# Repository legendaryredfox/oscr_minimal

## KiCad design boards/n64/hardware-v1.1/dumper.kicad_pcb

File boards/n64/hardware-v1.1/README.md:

# n64 v1.1

Versão **v1.1** da placa [`n64`](../README.md): shield 100% THT para Arduino Mega 2560 R3, só USB. Esta é a versão mais nova.

| | |
|---|---|
| Slots | N64 (50 pinos), 3,3 V |
| Circuitos | Si5351 só para a EEPROM. |
| Tamanho | 110,1 × 90,1 mm |
| Desligar o 5V por software | **sim** |
| Projeto KiCad | [`hardware-v1.1/`](.) (`dumper.kicad_pro`, `.kicad_sch`, `.kicad_pcb`) |
| Fábrica (JLCPCB) | `../fab/gerbers-v1.1/`, `../fab/dumper-v1.1-jlcpcb.zip` |
| Renders | `render-cima.png`, `render-baixo.png` |
| Estado | Nada montado nem testado com cartucho; revisar o layout no KiCad antes de encomendar |

## Troca de cartucho

**Com desligamento por software** (bloco de troca de cartucho, D126): o comando `POWER` liga e desliga o 5V dos slots, o rail é descarregado e o LED amarelo "SEGURO TROCAR" acende quando dá para tirar o cartucho. Circuito, peças e testes: [`docs/referencia/bloco-troca.md`](../../../docs/referencia/bloco-troca.md).

## Proteção de corrente e tensão (D138)

**F1: fusível de vidro 5×20 mm de 500 mA (ação rápida) em suporte de clipes, opcional.** O suporte é de furo passante (Littelfuse série 100 ou equivalente) e o fusível queimado se troca **sem solda**; fica em série com o 5 V que a placa recebe do Mega (nas versões com bloco de troca, antes do Q1). Um curto no cartucho queima o fusível e protege a placa, o Mega e a porta USB. A queda é de 0,1 a 0,2 V a 200 mA (o SA-1 do SNES continua abaixo de ~5,2 V). **Sem o fusível no suporte a placa fica sem 5 V** (um fio no lugar dele também serve). Ele limita corrente e não protege contra tensão errada.

## O que muda em relação à v1.0

| Peça | Referências | Antes | Agora |
|---|---|---|---|
| LED verde 3mm | D2 | 0 | 1 |
| LED amarelo 3mm | D3 | 0 | 1 |
| IRF9540N | Q1 | 0 | 1 |
| 2N7000 | Q2,Q3 | 0 | 2 |
| 100k | R3,R8 | 0 | 2 |
| 100R | R4 | 0 | 1 |
| 1k | R5,R9,R10 | 0 | 3 |
| 330R | R6,R7 | 0 | 2 |

## Lista de peças

| Referências | Valor | Footprint | Qtd |
|---|---|---|---|
| A1 | Mega2560_R3_Shield | `dumper:Mega2560_R3_Shield` | 1 |
| C1 | 470u/16V | `Capacitor_THT:CP_Radial_D8.0mm_P3.50mm` | 1 |
| C2,C3 | 1u | `Capacitor_THT:C_Disc_D5.0mm_W2.5mm_P5.00mm` | 2 |
| C4 | 100n | `Capacitor_THT:C_Disc_D5.0mm_W2.5mm_P5.00mm` | 1 |
| D1 | LED 3mm | `LED_THT:LED_D3.0mm` | 1 |
| D2 | LED verde 3mm | `LED_THT:LED_D3.0mm` | 1 |
| D3 | LED amarelo 3mm | `LED_THT:LED_D3.0mm` | 1 |
| F1 | Fusivel 5x20 500mA | `Fuse:Fuseholder_Littelfuse_100_series_5x20mm` | 1 |
| FLG1,FLG2 | PWR_FLAG | `` | 2 |
| N64_1 | N64_Slot | `dumper:N64_Slot` | 1 |
| Q1 | IRF9540N | `Package_TO_SOT_THT:TO-220-3_Vertical` | 1 |
| Q2,Q3 | 2N7000 | `Package_TO_SOT_THT:TO-92_Inline` | 2 |
| R1 | 220R | `Resistor_THT:R_Axial_DIN0207_L6.3mm_D2.5mm_P10.16mm_Horizontal` | 1 |
| R2 | 1k | `Resistor_THT:R_Axial_DIN0207_L6.3mm_D2.5mm_P10.16mm_Horizontal` | 1 |
| R3,R8 | 100k | `Resistor_THT:R_Axial_DIN0204_L3.6mm_D1.6mm_P2.54mm_Vertical` | 2 |
| R4 | 100R | `Resistor_THT:R_Axial_DIN0204_L3.6mm_D1.6mm_P2.54mm_Vertical` | 1 |
| R5,R9,R10 | 1k | `Resistor_THT:R_Axial_DIN0204_L3.6mm_D1.6mm_P2.54mm_Vertical` | 3 |
| R6,R7 | 330R | `Resistor_THT:R_Axial_DIN0204_L3.6mm_D1.6mm_P2.54mm_Vertical` | 2 |
| U1 | Si5351_Module | `Connector_PinSocket_2.54mm:PinSocket_1x07_P2.54mm_Vertical` | 1 |
| U2 | MCP1700-3302E/TO (3,3 V) | `Package_TO_SOT_THT:TO-92` | 1 |

Gerada do esquemático desta versão (`kicad-cli sch export bom`). Peças marcadas DNP ou opcionais: `docs/componentes-opcionais.md` da placa.

## Verificação e fábrica (da raiz do repositório)

```
python3 tools/check_netlist.py --board n64
kicad-cli sch erc boards/n64/hardware-v1.1/dumper.kicad_sch
kicad-cli pcb drc boards/n64/hardware-v1.1/dumper.kicad_pcb
tools/export_fab.sh n64 v1.1
tools/render_board.sh n64 v1.0 v1.1
```

Mais: [README da placa](../README.md), [`docs/`](../docs/).

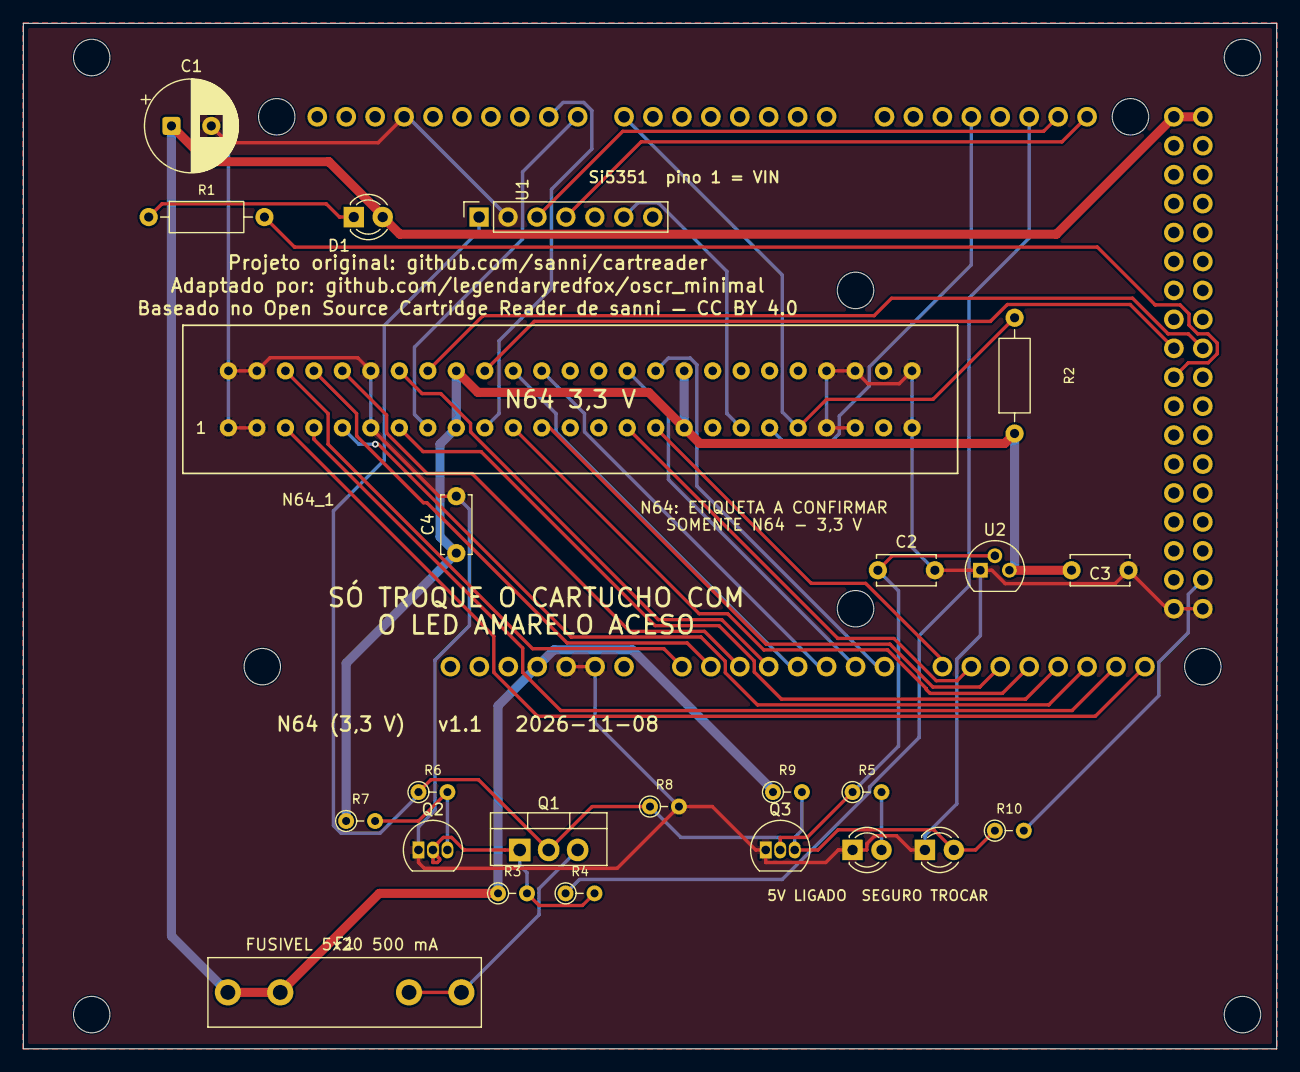
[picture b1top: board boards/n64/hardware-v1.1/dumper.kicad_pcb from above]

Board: 2 copper layers, 110.0 x 90.0 mm, 29 parts (0 on the bottom side), 38 nets.

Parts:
A1: Mega2560_R3_Shield
C1: 470u/16V; CP_Radial_D8.0mm_P3.50mm
C2, C3: 1u; C_Disc_D5.0mm_W2.5mm_P5.00mm
C4: 100n; C_Disc_D5.0mm_W2.5mm_P5.00mm
D1: LED 3mm; LED_D3.0mm
D2: LED verde 3mm; LED_D3.0mm
D3: LED amarelo 3mm; LED_D3.0mm
F1: Fusivel 5x20 500mA; Fuseholder_Littelfuse_100_series_5x20mm
MH1, MH2, MH3, MH4: MountingHole_3.2mm; MountingHole_3.2mm_M3
N64_1: N64_Slot
Q1: IRF9540N; TO-220-3_Vertical
Q2, Q3: 2N7000; TO-92_Inline
R1: 220R; R_Axial_DIN0207_L6.3mm_D2.5mm_P10.16mm_Horizontal
R2: 1k; R_Axial_DIN0207_L6.3mm_D2.5mm_P10.16mm_Horizontal
R3, R8: 100k; R_Axial_DIN0204_L3.6mm_D1.6mm_P2.54mm_Vertical
R4: 100R; R_Axial_DIN0204_L3.6mm_D1.6mm_P2.54mm_Vertical
R5, R9, R10: 1k; R_Axial_DIN0204_L3.6mm_D1.6mm_P2.54mm_Vertical
R6, R7: 330R; R_Axial_DIN0204_L3.6mm_D1.6mm_P2.54mm_Vertical
U1: Si5351_Module; PinSocket_1x07_P2.54mm_Vertical
U2: MCP1700-3302E/TO (3,3 V); TO-92

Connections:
+3V3: C3.1, C4.1, N64_1.9, N64_1.17, N64_1.34, N64_1.42, R2.1, R7.1, U2.3
+5V: A1.5V1, A1.5V3, A1.5V4, C1.1, D1.2, F1.1, R3.1, R9.1
+5V_CART: C2.1, Q1.2, Q3.2, R5.1, R6.1, R8.1, U1.1, U2.2
+5V_F: F1.2, Q1.3
/A0: A1.A0, N64_1.28
/A1: A1.A1, N64_1.29
/A2: A1.A2, N64_1.30
/A3: A1.A3, N64_1.32
/A4: A1.A4, N64_1.36
/A5: A1.A5, N64_1.37
/A6: A1.A6, N64_1.40
/A7: A1.A7, N64_1.41
/A8: A1.A8, N64_1.16
/A9: A1.A9, N64_1.15
/A10: A1.A10, N64_1.12
/A11: A1.A11, N64_1.11
/A12: A1.A12, N64_1.7
/A13: A1.A13, N64_1.5
/A14: A1.A14, N64_1.4
/A15: A1.A15, N64_1.3
/CLK1: N64_1.19, U1.6
/D7: A1.D7, N64_1.21, R2.2
/D8: A1.D8, N64_1.8
/D9: A1.D9, N64_1.10
/D17: A1.D17, N64_1.20
/D36: A1.D36, N64_1.35
/D37: A1.D37, N64_1.33
/PWR_EN: A1.D19, R4.1
/PWR_G: Q1.1, Q2.2, R3.2, R4.2
/SENSE: D3.2, Q3.3, R9.2, R10.1
/SENSE_MCU: A1.D53, R10.2
GND: A1.GND1, A1.GND2, A1.GND3, A1.GND5, A1.GND6, C1.2, C2.2, C3.2, C4.2, D2.1, D3.1, N64_1.1, N64_1.2, N64_1.6, N64_1.22, N64_1.23, N64_1.25, N64_1.26, N64_1.27, N64_1.31, N64_1.47, N64_1.48, N64_1.50, Q2.1, Q3.1, R8.2, U1.2, U2.1
unnamed: A1.D38, R1.2
unnamed: D1.1, R1.1
unnamed: D2.2, R5.2
unnamed: Q2.3, R6.2, R7.2
unnamed: A1.D21, U1.4
unnamed: A1.D20, U1.3

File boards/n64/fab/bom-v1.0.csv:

"Ref","Valor","Footprint","Qtd"
"A1","Mega2560_R3_Shield","dumper:Mega2560_R3_Shield","1"
"C1","470u/16V","Capacitor_THT:CP_Radial_D8.0mm_P3.50mm","1"
"C2,C3","1u","Capacitor_THT:C_Disc_D5.0mm_W2.5mm_P5.00mm","2"
"C4","100n","Capacitor_THT:C_Disc_D5.0mm_W2.5mm_P5.00mm","1"
"D1","LED 3mm","LED_THT:LED_D3.0mm","1"
"F1","Fusivel 5x20 500mA","Fuse:Fuseholder_Littelfuse_100_series_5x20mm","1"
"FLG1,FLG2","PWR_FLAG","","2"
"N64_1","N64_Slot","dumper:N64_Slot","1"
"R1","220R","Resistor_THT:R_Axial_DIN0207_L6.3mm_D2.5mm_P10.16mm_Horizontal","1"
"R2","1k","Resistor_THT:R_Axial_DIN0207_L6.3mm_D2.5mm_P10.16mm_Horizontal","1"
"U1","Si5351_Module","Connector_PinSocket_2.54mm:PinSocket_1x07_P2.54mm_Vertical","1"
"U2","MCP1700-3302E/TO (3,3 V)","Package_TO_SOT_THT:TO-92","1"

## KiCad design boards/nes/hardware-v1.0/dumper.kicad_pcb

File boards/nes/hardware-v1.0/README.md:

# nes v1.0

Versão **v1.0** da placa [`nes`](../README.md): shield 100% THT para Arduino Mega 2560 R3, só USB. Versão anterior, mantida ao lado da mais nova.

| | |
|---|---|
| Slots | NES (72p, 2,5 mm), 5 V |
| Circuitos | Si5351 (clock do slot), sem PIC. |
| Tamanho | 110,1 × 61,1 mm |
| Projeto KiCad | [`hardware-v1.0/`](.) (`dumper.kicad_pro`, `.kicad_sch`, `.kicad_pcb`) |
| Fábrica (JLCPCB) | `../fab/gerbers-v1.0/`, `../fab/dumper-v1.0-jlcpcb.zip` |
| Renders | `render-cima.png`, `render-baixo.png` |
| Mecânica | Sem os 6 furos M3 do Mega (só os 4 furos de canto); F1 entre o slot e o header do Mega, sem a faixa extra de baixo (D141) |
| Estado | Nada montado nem testado com cartucho; revisar o layout no KiCad antes de encomendar |

## Troca de cartucho

O 5V dos slots vai direto do Mega e **não é cortado por software** (o desligamento por software foi retirado, D139). Para trocar o cartucho, **desligue a placa tirando o cabo USB** do Mega; nunca com a USB ligada.

## Proteção de corrente e tensão (D138)

**F1: fusível de vidro 5×20 mm de 500 mA (ação rápida) em suporte de clipes, opcional.** O suporte é de furo passante (Littelfuse série 100 ou equivalente) e o fusível queimado se troca **sem solda**; fica em série com o 5 V que a placa recebe do Mega Um curto no cartucho queima o fusível e protege a placa, o Mega e a porta USB. A queda é de 0,1 a 0,2 V a 200 mA (o SA-1 do SNES continua abaixo de ~5,2 V). **Sem o fusível no suporte a placa fica sem 5 V** (um fio no lugar dele também serve). Ele limita corrente e não protege contra tensão errada.

## Lista de peças

| Referências | Valor | Footprint | Qtd |
|---|---|---|---|
| A1 | Mega2560_R3_Shield | `dumper:Mega2560_R3_Shield` | 1 |
| C1 | 470u/16V | `Capacitor_THT:CP_Radial_D8.0mm_P3.50mm` | 1 |
| C2 | 100n | `Capacitor_THT:C_Disc_D5.0mm_W2.5mm_P5.00mm` | 1 |
| D1 | LED 3mm | `LED_THT:LED_D3.0mm` | 1 |
| F1 | Fusivel 5x20 500mA | `Fuse:Fuseholder_Littelfuse_100_series_5x20mm` | 1 |
| FLG1,FLG2 | PWR_FLAG | `` | 2 |
| NES1 | NES_Slot | `dumper:NES_Slot` | 1 |
| R1 | 220R | `Resistor_THT:R_Axial_DIN0207_L6.3mm_D2.5mm_P10.16mm_Horizontal` | 1 |
| U1 | Si5351_Module | `Connector_PinSocket_2.54mm:PinSocket_1x07_P2.54mm_Vertical` | 1 |

Gerada do esquemático desta versão (`kicad-cli sch export bom`). Peças marcadas DNP ou opcionais: `docs/bom.md` da placa.

## Verificação e fábrica (da raiz do repositório)

```
python3 tools/check_netlist.py --board nes boards/nes/hardware-v1.0/dumper.kicad_sch
kicad-cli sch erc boards/nes/hardware-v1.0/dumper.kicad_sch
kicad-cli pcb drc boards/nes/hardware-v1.0/dumper.kicad_pcb
tools/export_fab.sh nes v1.0
tools/render_board.sh nes v1.0 v1.1
```

Mais: [README da placa](../README.md), [`docs/`](../docs/).

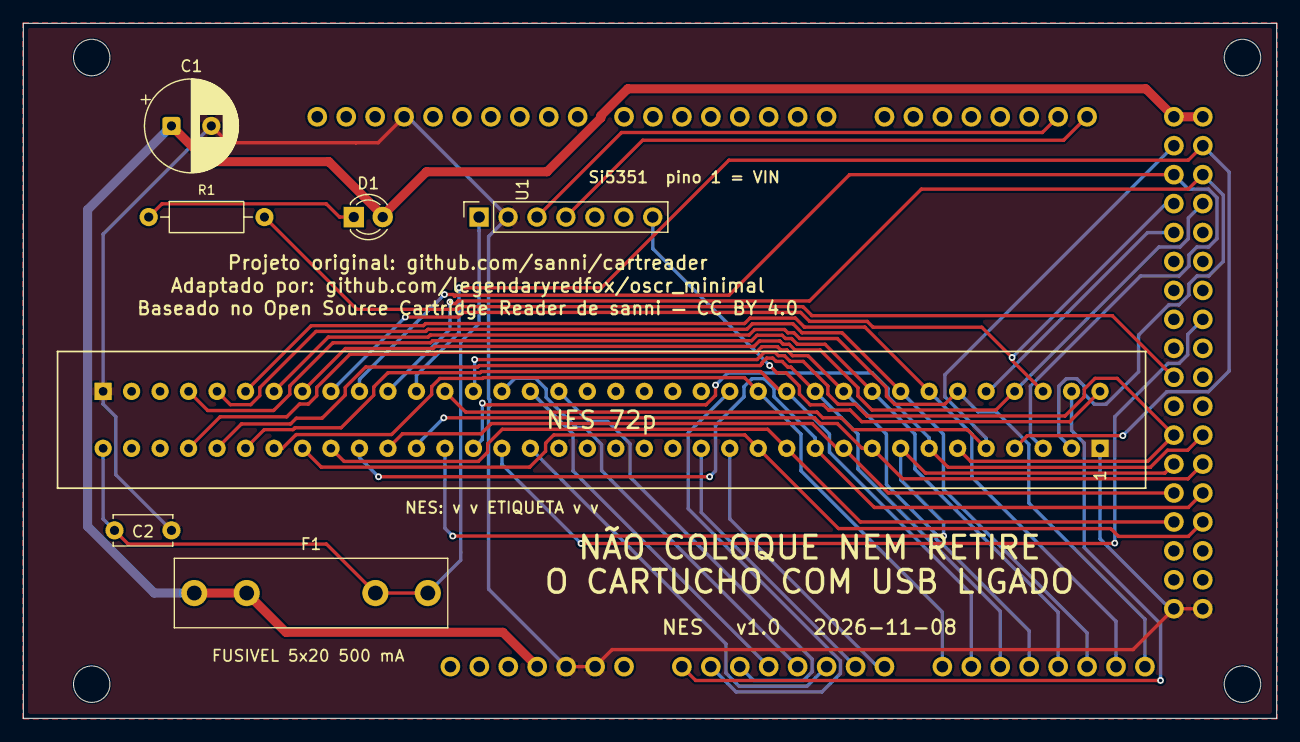
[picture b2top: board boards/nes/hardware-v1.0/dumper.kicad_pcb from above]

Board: 2 copper layers, 110.0 x 61.0 mm, 12 parts (0 on the bottom side), 40 nets.

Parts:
A1: Mega2560_R3_Shield
C1: 470u/16V; CP_Radial_D8.0mm_P3.50mm
C2: 100n; C_Disc_D5.0mm_W2.5mm_P5.00mm
D1: LED 3mm; LED_D3.0mm
F1: Fusivel 5x20 500mA; Fuseholder_Littelfuse_100_series_5x20mm
MH1, MH2, MH3, MH4: MountingHole_3.2mm; MountingHole_3.2mm_M3
NES1: NES_Slot
R1: 220R; R_Axial_DIN0207_L6.3mm_D2.5mm_P10.16mm_Horizontal
U1: Si5351_Module; PinSocket_1x07_P2.54mm_Vertical

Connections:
+5V: A1.5V1, A1.5V3, A1.5V4, C1.1, D1.2, F1.1
+5V_CART: C2.1, F1.2, NES1.36, U1.1
/A0: A1.A0, NES1.38
/A1: A1.A1, NES1.50
/A2: A1.A2, NES1.56
/A3: A1.A3, NES1.57
/A4: A1.A4, NES1.58
/A5: A1.A5, NES1.21
/A6: A1.A6, NES1.15
/A7: A1.A7, NES1.14
/A8: A1.A8, NES1.30, NES1.49
/A9: A1.A9, NES1.31, NES1.48
/A10: A1.A10, NES1.32, NES1.47
/A11: A1.A11, NES1.33, NES1.46
/A12: A1.A12, NES1.45, NES1.69
/A13: A1.A13, NES1.44, NES1.68
/A14: A1.A14, NES1.43, NES1.67
/A15: A1.A15, NES1.42, NES1.66
/CLK0: NES1.37, U1.7
/D22: A1.D22, NES1.5, NES1.60
/D23: A1.D23, NES1.4, NES1.61
/D24: A1.D24, NES1.3, NES1.63
/D25: A1.D25, NES1.2, NES1.62
/D26: A1.D26, NES1.39, NES1.64
/D27: A1.D27, NES1.40, NES1.65
/D28: A1.D28, NES1.41
/D35: A1.D35, NES1.22
/D42: A1.D42, NES1.6, NES1.59
/D43: A1.D43, NES1.7, NES1.23
/D44: A1.D44, NES1.8, NES1.24
/D45: A1.D45, NES1.9, NES1.25
/D46: A1.D46, NES1.10, NES1.26
/D47: A1.D47, NES1.11, NES1.27
/D48: A1.D48, NES1.12, NES1.28
/D49: A1.D49, NES1.13, NES1.29
GND: A1.GND1, A1.GND2, A1.GND3, A1.GND5, A1.GND6, C1.2, C2.2, NES1.1, NES1.72, U1.2
unnamed: A1.D38, R1.2
unnamed: D1.1, R1.1
unnamed: A1.D21, U1.4
unnamed: A1.D20, U1.3

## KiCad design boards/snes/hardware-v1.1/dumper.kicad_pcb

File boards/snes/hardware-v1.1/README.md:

# snes v1.1

Versão **v1.1** da placa [`snes`](../README.md): shield 100% THT para Arduino Mega 2560 R3, só USB. Esta é a versão mais nova.

| | |
|---|---|
| Slots | SNES (62p, 2,5 mm), 5 V |
| Circuitos | Si5351 em header fêmea e PIC12F629 (CIC) em soquete. |
| Tamanho | 107,1 × 90,1 mm |
| Desligar o 5V por software | **sim** |
| Projeto KiCad | [`hardware-v1.1/`](.) (`dumper.kicad_pro`, `.kicad_sch`, `.kicad_pcb`) |
| Fábrica (JLCPCB) | `../fab/gerbers-v1.1/`, `../fab/dumper-v1.1-jlcpcb.zip` |
| Renders | `render-cima.png`, `render-baixo.png` |
| Estado | Nada montado nem testado com cartucho; revisar o layout no KiCad antes de encomendar |

## Troca de cartucho

**Com desligamento por software** (bloco de troca de cartucho, D126): o comando `POWER` liga e desliga o 5V dos slots, o rail é descarregado e o LED amarelo "SEGURO TROCAR" acende quando dá para tirar o cartucho. Circuito, peças e testes: [`docs/referencia/bloco-troca.md`](../../../docs/referencia/bloco-troca.md).

## Proteção de corrente e tensão (D138)

**F1: fusível de vidro 5×20 mm de 500 mA (ação rápida) em suporte de clipes, opcional.** O suporte é de furo passante (Littelfuse série 100 ou equivalente) e o fusível queimado se troca **sem solda**; fica em série com o 5 V que a placa recebe do Mega (nas versões com bloco de troca, antes do Q1). Um curto no cartucho queima o fusível e protege a placa, o Mega e a porta USB. A queda é de 0,1 a 0,2 V a 200 mA (o SA-1 do SNES continua abaixo de ~5,2 V). **Sem o fusível no suporte a placa fica sem 5 V** (um fio no lugar dele também serve). Ele limita corrente e não protege contra tensão errada.

## O que muda em relação à v1.0

| Peça | Referências | Antes | Agora |
|---|---|---|---|
| LED verde 3mm | D2 | 0 | 1 |
| LED amarelo 3mm | D3 | 0 | 1 |
| IRF9540N | Q1 | 0 | 1 |
| 2N7000 | Q2,Q3 | 0 | 2 |
| 100k | R3,R7 | 0 | 2 |
| 100R | R4 | 0 | 1 |
| 1k | R5,R8,R9 | 0 | 3 |
| 330R | R6 | 0 | 1 |

## Lista de peças

| Referências | Valor | Footprint | Qtd |
|---|---|---|---|
| A1 | Mega2560_R3_Shield | `dumper:Mega2560_R3_Shield` | 1 |
| C1 | 470u/16V | `Capacitor_THT:CP_Radial_D8.0mm_P3.50mm` | 1 |
| C2,C3 | 100n | `Capacitor_THT:C_Disc_D5.0mm_W2.5mm_P5.00mm` | 2 |
| D1 | LED 3mm | `LED_THT:LED_D3.0mm` | 1 |
| D2 | LED verde 3mm | `LED_THT:LED_D3.0mm` | 1 |
| D3 | LED amarelo 3mm | `LED_THT:LED_D3.0mm` | 1 |
| F1 | Fusivel 5x20 500mA | `Fuse:Fuseholder_Littelfuse_100_series_5x20mm` | 1 |
| FLG1,FLG2 | PWR_FLAG | `` | 2 |
| Q1 | IRF9540N | `Package_TO_SOT_THT:TO-220-3_Vertical` | 1 |
| Q2,Q3 | 2N7000 | `Package_TO_SOT_THT:TO-92_Inline` | 2 |
| R1 | 220R | `Resistor_THT:R_Axial_DIN0207_L6.3mm_D2.5mm_P10.16mm_Horizontal` | 1 |
| R2 | 1k | `Resistor_THT:R_Axial_DIN0207_L6.3mm_D2.5mm_P10.16mm_Horizontal` | 1 |
| R3,R7 | 100k | `Resistor_THT:R_Axial_DIN0204_L3.6mm_D1.6mm_P2.54mm_Vertical` | 2 |
| R4 | 100R | `Resistor_THT:R_Axial_DIN0204_L3.6mm_D1.6mm_P2.54mm_Vertical` | 1 |
| R5,R8,R9 | 1k | `Resistor_THT:R_Axial_DIN0204_L3.6mm_D1.6mm_P2.54mm_Vertical` | 3 |
| R6 | 330R | `Resistor_THT:R_Axial_DIN0204_L3.6mm_D1.6mm_P2.54mm_Vertical` | 1 |
| SNES1 | SNES_Slot | `dumper:SNES_Slot` | 1 |
| U1 | Si5351_Module | `Connector_PinSocket_2.54mm:PinSocket_1x07_P2.54mm_Vertical` | 1 |
| U2 | PIC12F629 (em soquete; snescic-lock-resync) | `Package_DIP:DIP-8_W7.62mm` | 1 |

Gerada do esquemático desta versão (`kicad-cli sch export bom`). Peças marcadas DNP ou opcionais: `docs/componentes-opcionais.md` da placa.

## Verificação e fábrica (da raiz do repositório)

```
python3 tools/check_netlist.py --board snes
kicad-cli sch erc boards/snes/hardware-v1.1/dumper.kicad_sch
kicad-cli pcb drc boards/snes/hardware-v1.1/dumper.kicad_pcb
tools/export_fab.sh snes v1.1
tools/render_board.sh snes v1.0 v1.1
```

Mais: [README da placa](../README.md), [`docs/`](../docs/).

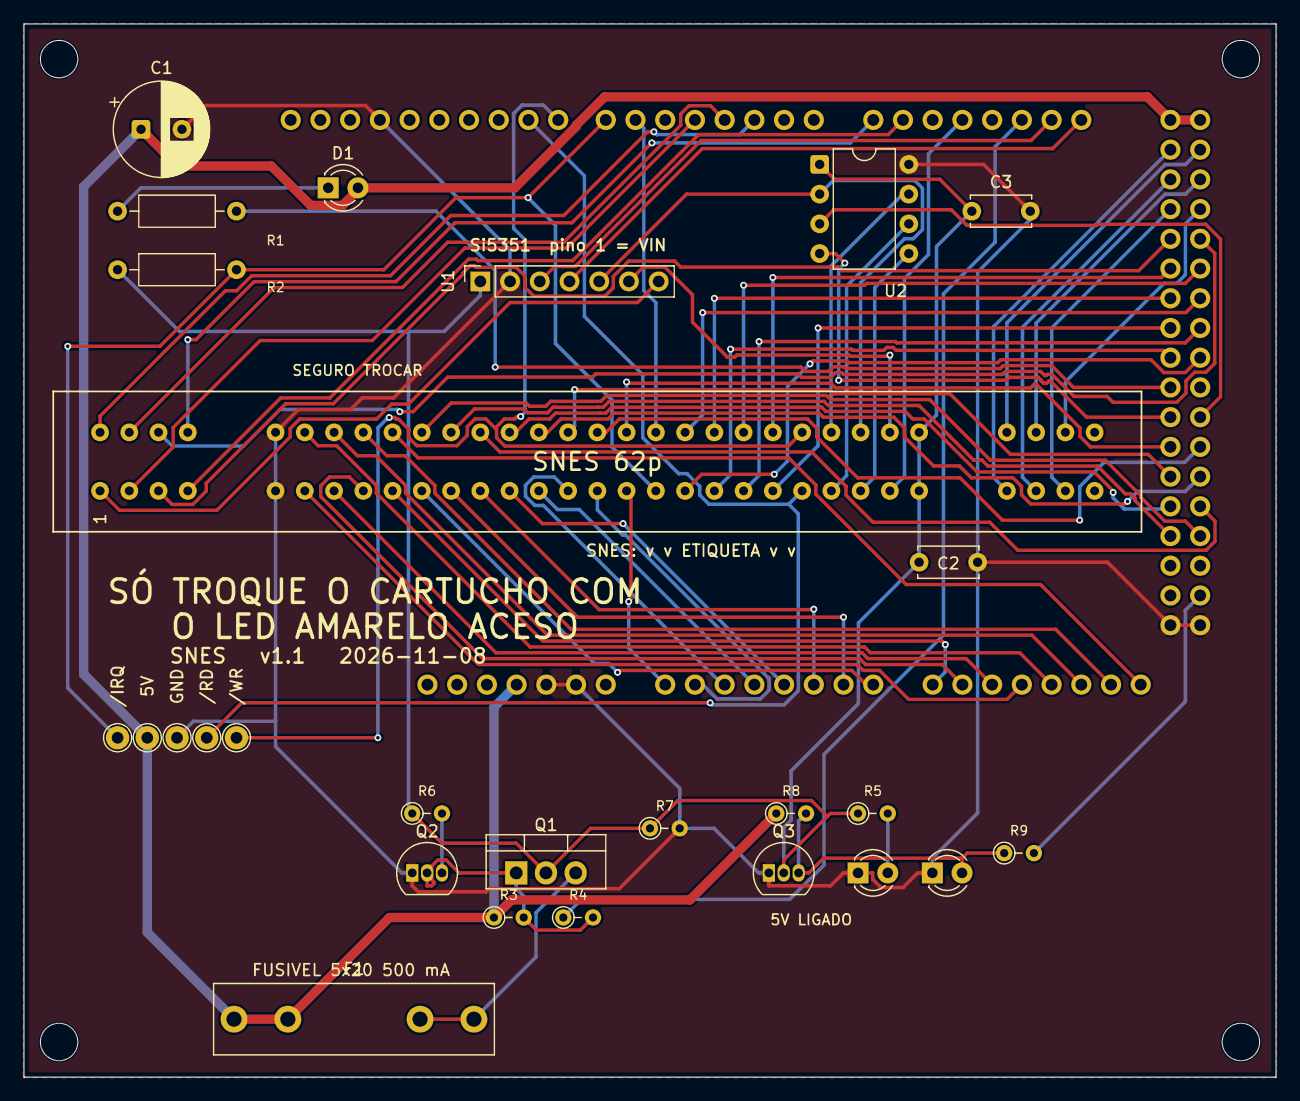
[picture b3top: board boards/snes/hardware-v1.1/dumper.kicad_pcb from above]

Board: 2 copper layers, 107.0 x 90.0 mm, 32 parts (0 on the bottom side), 72 nets.

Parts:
A1: Mega2560_R3_Shield
C1: 470u/16V; CP_Radial_D8.0mm_P3.50mm
C2, C3: 100n; C_Disc_D5.0mm_W2.5mm_P5.00mm
D1: LED 3mm; LED_D3.0mm
D2: LED verde 3mm; LED_D3.0mm
D3: LED amarelo 3mm; LED_D3.0mm
F1: Fusivel 5x20 500mA; Fuseholder_Littelfuse_100_series_5x20mm
MH1, MH2, MH3, MH4: MountingHole_3.2mm; MountingHole_3.2mm_M3
Q1: IRF9540N; TO-220-3_Vertical
Q2, Q3: 2N7000; TO-92_Inline
R1: 220R; R_Axial_DIN0207_L6.3mm_D2.5mm_P10.16mm_Horizontal
R2: 1k; R_Axial_DIN0207_L6.3mm_D2.5mm_P10.16mm_Horizontal
R3, R7: 100k; R_Axial_DIN0204_L3.6mm_D1.6mm_P2.54mm_Vertical
R4: 100R; R_Axial_DIN0204_L3.6mm_D1.6mm_P2.54mm_Vertical
R5, R8, R9: 1k; R_Axial_DIN0204_L3.6mm_D1.6mm_P2.54mm_Vertical
R6: 330R; R_Axial_DIN0204_L3.6mm_D1.6mm_P2.54mm_Vertical
SNES1: SNES_Slot
TP1: 5V; TestPoint_THTPad_D2.0mm_Drill1.0mm
TP2: GND; TestPoint_THTPad_D2.0mm_Drill1.0mm
TP3: /RD; TestPoint_THTPad_D2.0mm_Drill1.0mm
TP4: /WR; TestPoint_THTPad_D2.0mm_Drill1.0mm
TP5: /IRQ; TestPoint_THTPad_D2.0mm_Drill1.0mm
U1: Si5351_Module; PinSocket_1x07_P2.54mm_Vertical
U2: PIC12F629 (em soquete; snescic-lock-resync); DIP-8_W7.62mm

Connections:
+5V: A1.5V1, A1.5V3, A1.5V4, C1.1, D1.2, F1.1, R3.1, R8.1, TP1.1
+5V_CART: C2.1, C3.1, Q1.2, Q3.2, R2.1, R5.1, R6.1, R7.1, SNES1.27, SNES1.58, U1.1, U2.1
+5V_F: F1.2, Q1.3
/A0: A1.A0, SNES1.17
/A1: A1.A1, SNES1.16
/A2: A1.A2, SNES1.15
/A3: A1.A3, SNES1.14
/A4: A1.A4, SNES1.13
/A5: A1.A5, SNES1.12
/A6: A1.A6, SNES1.11
/A7: A1.A7, SNES1.10
/A8: A1.A8, SNES1.9
/A9: A1.A9, SNES1.8
/A10: A1.A10, SNES1.7
/A11: A1.A11, SNES1.6
/A12: A1.A12, SNES1.37
/A13: A1.A13, SNES1.38
/A14: A1.A14, SNES1.39
/A15: A1.A15, SNES1.40
/CIC_DATA_0: SNES1.55, U2.7
/CIC_DATA_1: SNES1.24, U2.6
/CIC_RESET: SNES1.25, U2.5
/CLK0: SNES1.1, U1.7
/CLK1: SNES1.57, U1.6
/CLK2: SNES1.56, U1.5, U2.2
/D2: A1.D2, SNES1.32
/D3: A1.D3, SNES1.33
/D4: A1.D4, SNES1.2
/D6: A1.D6, SNES1.49
/D7: A1.D7, R2.2, SNES1.18, TP5.1
/D8: A1.D8, SNES1.54, TP4.1
/D9: A1.D9, SNES1.23, TP3.1
/D14: A1.D14, SNES1.35
/D15: A1.D15, SNES1.4
/D17: A1.D17, SNES1.26
/D22: A1.D22, SNES1.28
/D23: A1.D23, SNES1.59
/D24: A1.D24, SNES1.29
/D25: A1.D25, SNES1.60
/D26: A1.D26, SNES1.30
/D27: A1.D27, SNES1.61
/D28: A1.D28, SNES1.3
/D29: A1.D29, SNES1.34
/D30: A1.D30, SNES1.53
/D31: A1.D31, SNES1.52
/D32: A1.D32, SNES1.51
/D33: A1.D33, SNES1.50
/D34: A1.D34, SNES1.22
/D35: A1.D35, SNES1.21
/D36: A1.D36, SNES1.20
/D37: A1.D37, SNES1.19
/D42: A1.D42, SNES1.48
/D43: A1.D43, SNES1.47
/D44: A1.D44, SNES1.46
/D45: A1.D45, SNES1.45
/D46: A1.D46, SNES1.44
/D47: A1.D47, SNES1.43
/D48: A1.D48, SNES1.42
/D49: A1.D49, SNES1.41
/PWR_EN: A1.D19, R4.1
/PWR_G: Q1.1, Q2.2, R3.2, R4.2
/SENSE: D3.2, Q3.3, R8.2, R9.1
/SENSE_MCU: A1.D53, R9.2
GND: A1.GND1, A1.GND2, A1.GND3, A1.GND5, A1.GND6, C1.2, C2.2, C3.2, D2.1, D3.1, Q2.1, Q3.1, R7.2, SNES1.5, SNES1.36, TP2.1, U1.2, U2.8
unnamed: A1.D38, R1.2
unnamed: D1.1, R1.1
unnamed: D2.2, R5.2
unnamed: Q2.3, R6.2
unnamed: A1.D21, U1.4
unnamed: A1.D20, U1.3
unnamed: A1.D40, U2.4
unnamed: A1.D41, U2.3

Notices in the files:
boards/n64/hardware-v1.1/dumper.kicad_pcb:
Baseado no Open Source Cartridge Reader de sanni — CC BY 4.0
